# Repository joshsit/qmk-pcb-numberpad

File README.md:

# qmk-pcb_numberpad
Project files for development of twelve key mechanical keyboard numberpad with custom PCB. 

2025-06-19, build v1:
- some of the switches were not seated fully (not flush to the pcb) when soldering, need to ensure fully seated for next iteration
- assembled keyboard looks a little funny without a top plate, need to figure out how to raise the rp2040 zero if wanting to add a top plate
- switches may come loose if just held on by soldering welds to the legs, might need to glue the support pins or add a top plate

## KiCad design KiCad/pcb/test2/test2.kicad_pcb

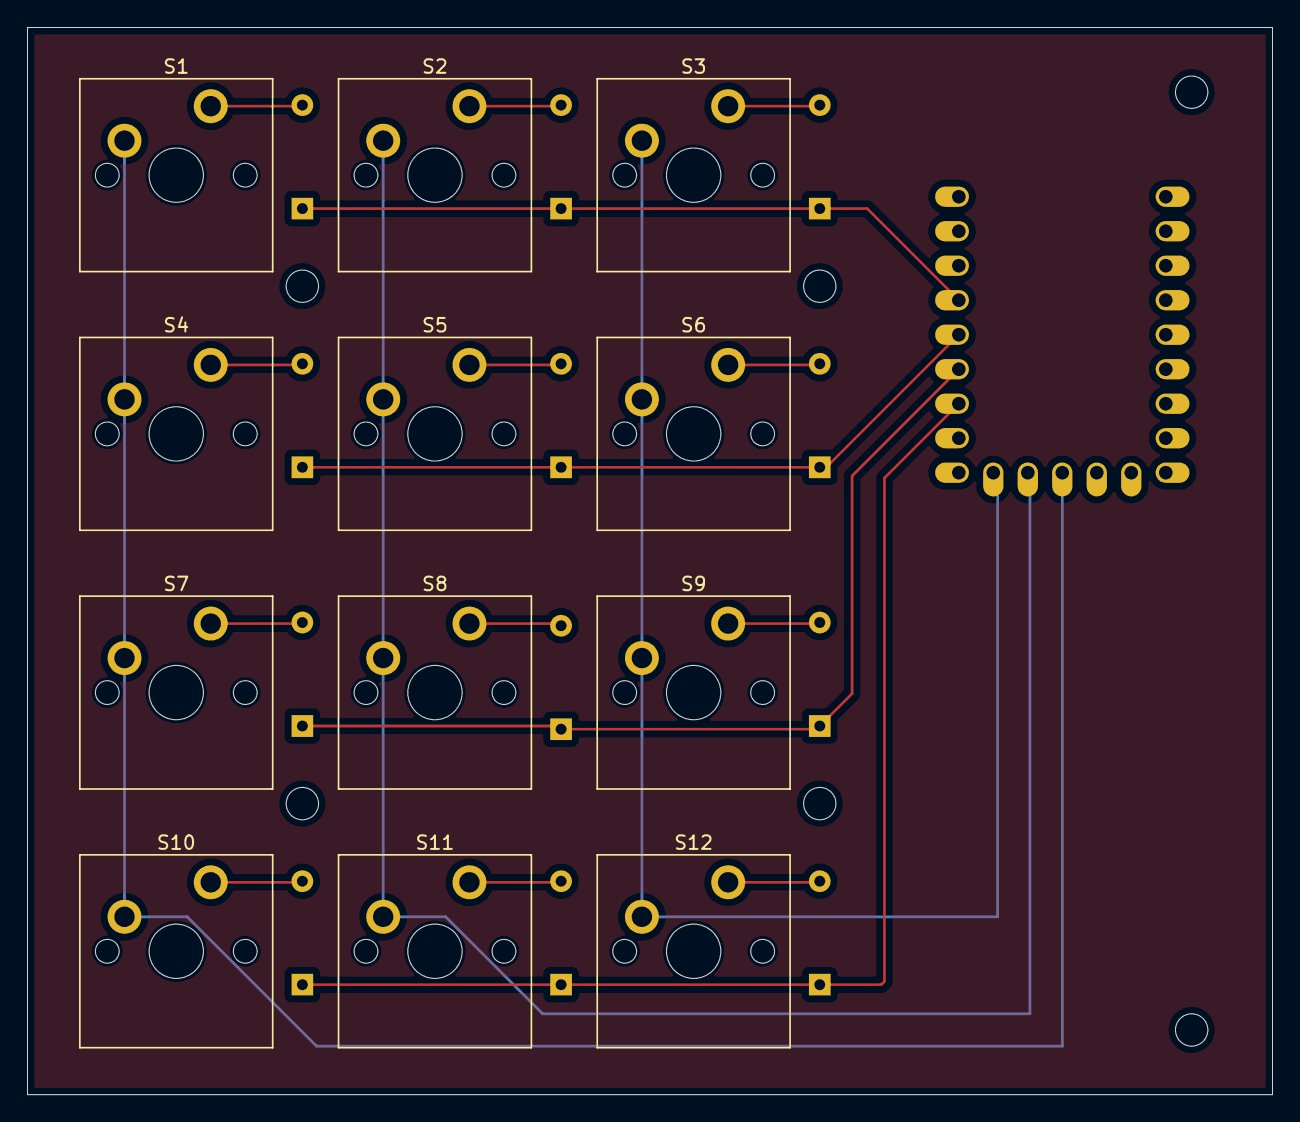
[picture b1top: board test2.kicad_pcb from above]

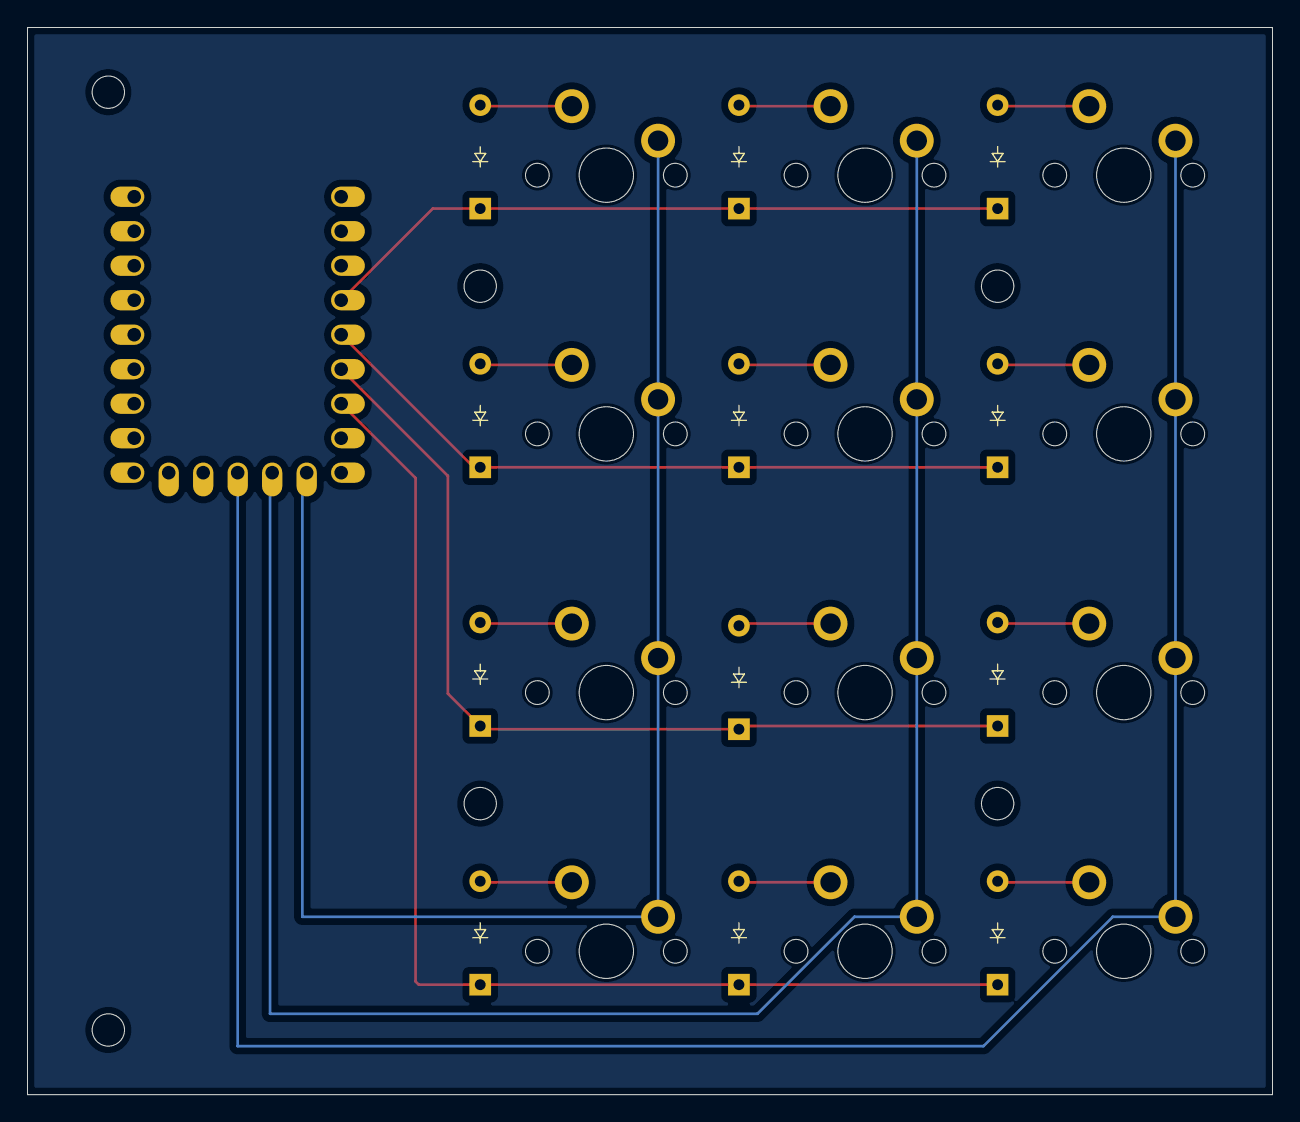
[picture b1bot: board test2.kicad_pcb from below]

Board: 2 copper layers, 91.7 x 78.6 mm, 25 parts (12 on the bottom side), 19 nets.

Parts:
D1, D2, D3, D4, D5, D6, D7, D8, D9, D10, D11, D12: Diode; Diode_DO-35
S1, S2, S3, S4, S5, S6, S7, S8, S9, S10, S11, S12: Keyswitch; MX_PCB_1.00u
U1: RP2040_Zero

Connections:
C0: S1.1, S4.1, S7.1, S10.1, U1.12 (11)
C1: S2.1, S5.1, S8.1, S11.1, U1.13 (12)
C2: S3.1, S6.1, S9.1, S12.1, U1.14 (13)
unnamed: D1.2 (A), S1.2
unnamed: D2.2 (A), S2.2
unnamed: D3.2 (A), S3.2
unnamed: D4.2 (A), S4.2
unnamed: D5.2 (A), S5.2
unnamed: D6.2 (A), S6.2
unnamed: D7.2 (A), S7.2
unnamed: D8.2 (A), S8.2
unnamed: D9.2 (A), S9.2
unnamed: D10.2 (A), S10.2
unnamed: D11.2 (A), S11.2
unnamed: D12.2 (A), S12.2
R0: D1.1 (K), D2.1 (K), D3.1 (K), U1.20 (29)
R1: D4.1 (K), D5.1 (K), D6.1 (K), U1.19 (28)
R2: D7.1 (K), D8.1 (K), D9.1 (K), U1.18 (27)
R3: D10.1 (K), D11.1 (K), D12.1 (K), U1.17 (26)

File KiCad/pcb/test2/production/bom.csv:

Designator,Footprint,Quantity,Value,LCSC Part #
"D1, D10, D11, D12, D2, D3, D4, D5, D6, D7, D8, D9",Diode_DO-35,12,Diode,
"S1, S10, S11, S12, S2, S3, S4, S5, S6, S7, S8, S9",MX_PCB_1.00u,12,Keyswitch,
U1,RP2040_Zero,1,RP2040_Zero,

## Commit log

2025-06-19 Added kicad files
2025-06-19 organizing
2025-06-19 updates on build v1
2025-06-25 updated qmk files
2025-06-25 updating keymap with combos
